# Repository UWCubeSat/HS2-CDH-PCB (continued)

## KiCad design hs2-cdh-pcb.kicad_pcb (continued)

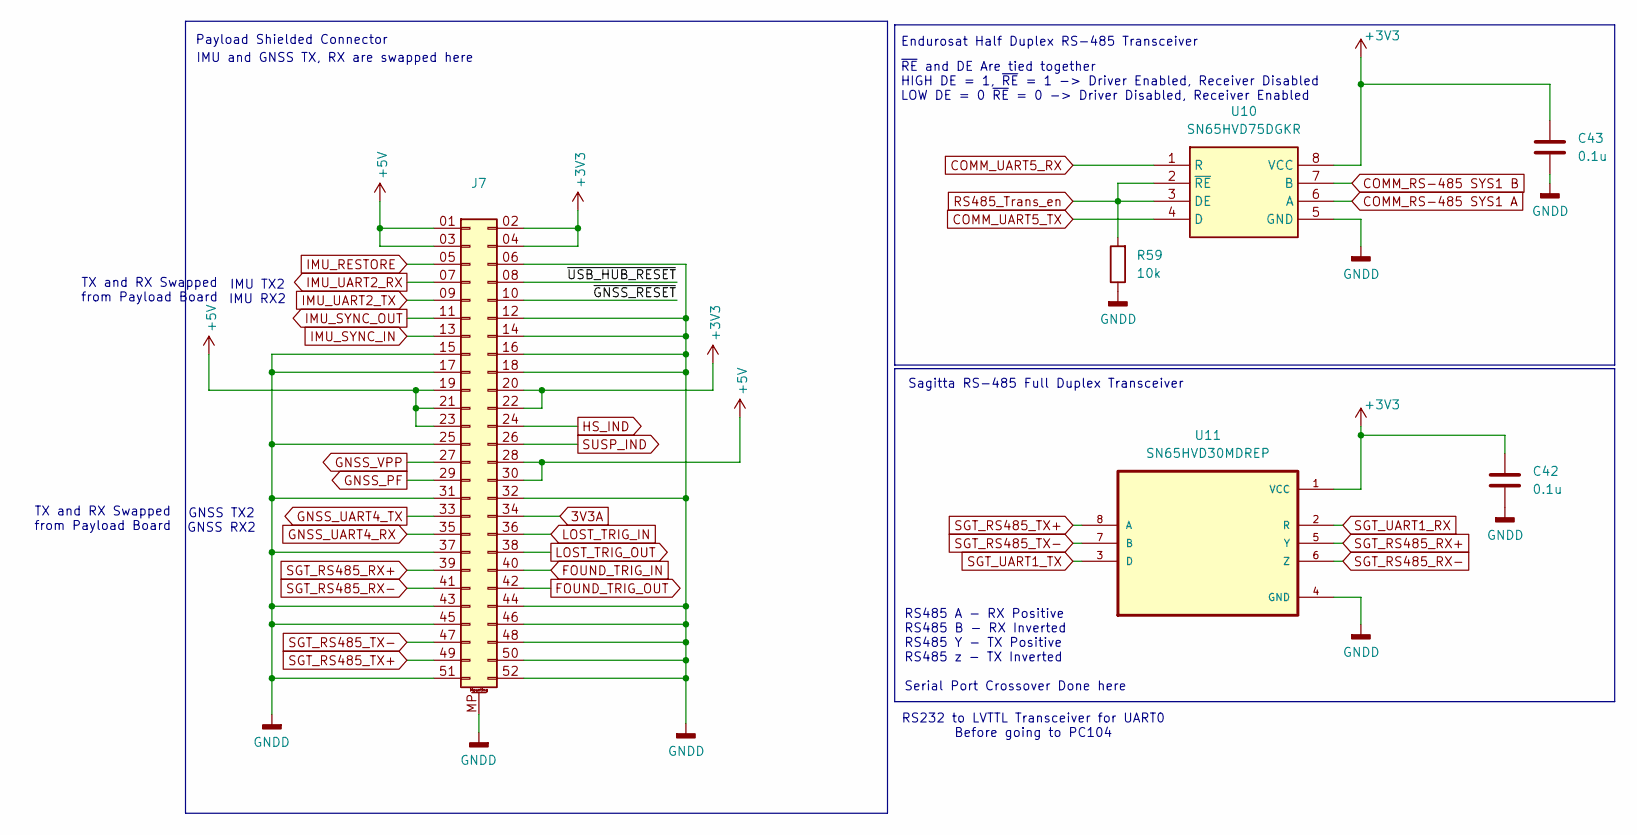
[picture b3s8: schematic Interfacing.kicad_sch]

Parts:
C42, C43: 0.1u; C_0603_1608Metric
J7: Conn_02x26_Odd_Even_MountingPin; SAMTEC_ASP-129637
R59: 10k; R_0603_1608Metric
U10: SN65HVD75DGKR; VSSOP-8_3x3mm_P0.65mm; Mouser Part Number 595-SN65HVD75DGKR
U11: SN65HVD30MDREP; SOIC-8_3.9x4.9mm_P1.27mm

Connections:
3V3A: J7.34; also elsewhere on the board
+3V3: C42.1, C43.1, J7.02 (Pin_2), J7.04 (Pin_4), J7.20, J7.22, U10.8 (VCC), U11.1 (VCC); also elsewhere on the board
+5V: J7.01 (Pin_1), J7.03 (Pin_3), J7.19, J7.21, J7.23, J7.28, J7.30; also elsewhere on the board
/Interfacing/~GNSS_RESET: J7.10
/Interfacing/~USB_HUB_RESET: J7.08 (Pin_8)
COMM_RS-485 SYS1 A: U10.6 (A); also elsewhere on the board
COMM_RS-485 SYS1 B: U10.7 (B); also elsewhere on the board
COMM_UART5_RX: U10.1 (R); also elsewhere on the board
COMM_UART5_TX: U10.4 (D); also elsewhere on the board
FOUND_TRIG_IN: J7.40; also elsewhere on the board
FOUND_TRIG_OUT: J7.42; also elsewhere on the board
GNDD: C42.2, C43.2, J7.06 (Pin_6), J7.12, J7.14, J7.15, J7.16, J7.17, J7.18, J7.25, J7.31, J7.32, J7.37, J7.43, J7.44, J7.45, J7.46, J7.48, J7.50, J7.51, J7.52, J7.MP (MountPin), R59.1, U10.5 (GND), U11.4 (GND); also elsewhere on the board
GNSS_PF: J7.29; also elsewhere on the board
GNSS_UART4_RX: J7.35; also elsewhere on the board
GNSS_UART4_TX: J7.33; also elsewhere on the board
GNSS_VPP: J7.27; also elsewhere on the board
HS_IND: J7.24; also elsewhere on the board
IMU_RESTORE: J7.05 (Pin_5)
IMU_SYNC_IN: J7.13; also elsewhere on the board
IMU_SYNC_OUT: J7.11; also elsewhere on the board
IMU_UART2_RX: J7.07 (Pin_7); also elsewhere on the board
IMU_UART2_TX: J7.09 (Pin_9); also elsewhere on the board
LOST_TRIG_IN: J7.36; also elsewhere on the board
LOST_TRIG_OUT: J7.38; also elsewhere on the board
RS485_Trans_en: R59.2, U10.2 (~RE), U10.3 (DE); also elsewhere on the board
SGT_RS485_RX+: J7.39, U11.5 (Y)
SGT_RS485_RX-: J7.41, U11.6 (Z)
SGT_RS485_TX+: J7.49, U11.8 (A)
SGT_RS485_TX-: J7.47, U11.7 (B)
SGT_UART1_RX: U11.2 (R); also elsewhere on the board
SGT_UART1_TX: U11.3 (D); also elsewhere on the board
SUSP_IND: J7.26; also elsewhere on the board

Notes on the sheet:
Sagitta RS-485 Full Duplex Transceiver
Payload Shielded Connector
IMU TX2 IMU RX2
GNSS TX2 GNSS RX2
TX and RX Swapped from Payload Board
~{RE} and DE Are tied together HIGH DE = 1, ~{RE} = 1 -> Driver Enabled, Receiver Disabled LOW DE = 0 ~{RE} = 0 -> Driver Disabled, Receiver Enabled
Endurosat Half Duplex RS-485 Transceiver
RS232 to LVTTL Transceiver for UART0 Before going to PC104
RS485 A - RX Positive RS485 B - RX Inverted RS485 Y - TX Positive RS485 z - TX Inverted Serial Port Crossover Done here
IMU and GNSS TX, RX are swapped here

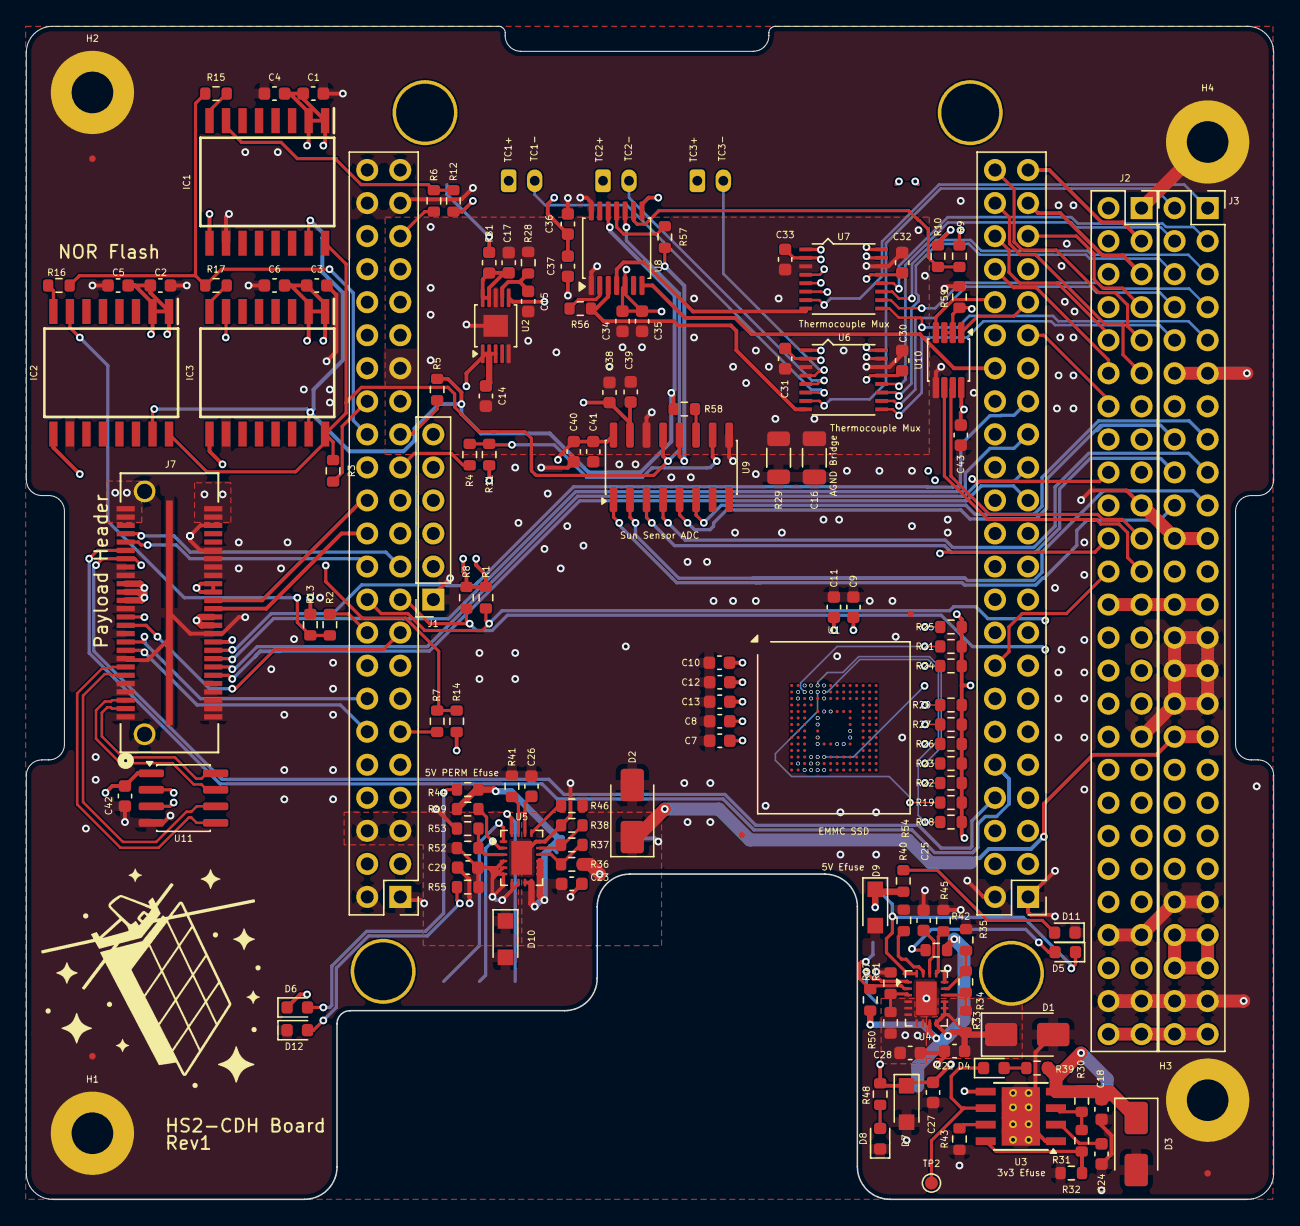
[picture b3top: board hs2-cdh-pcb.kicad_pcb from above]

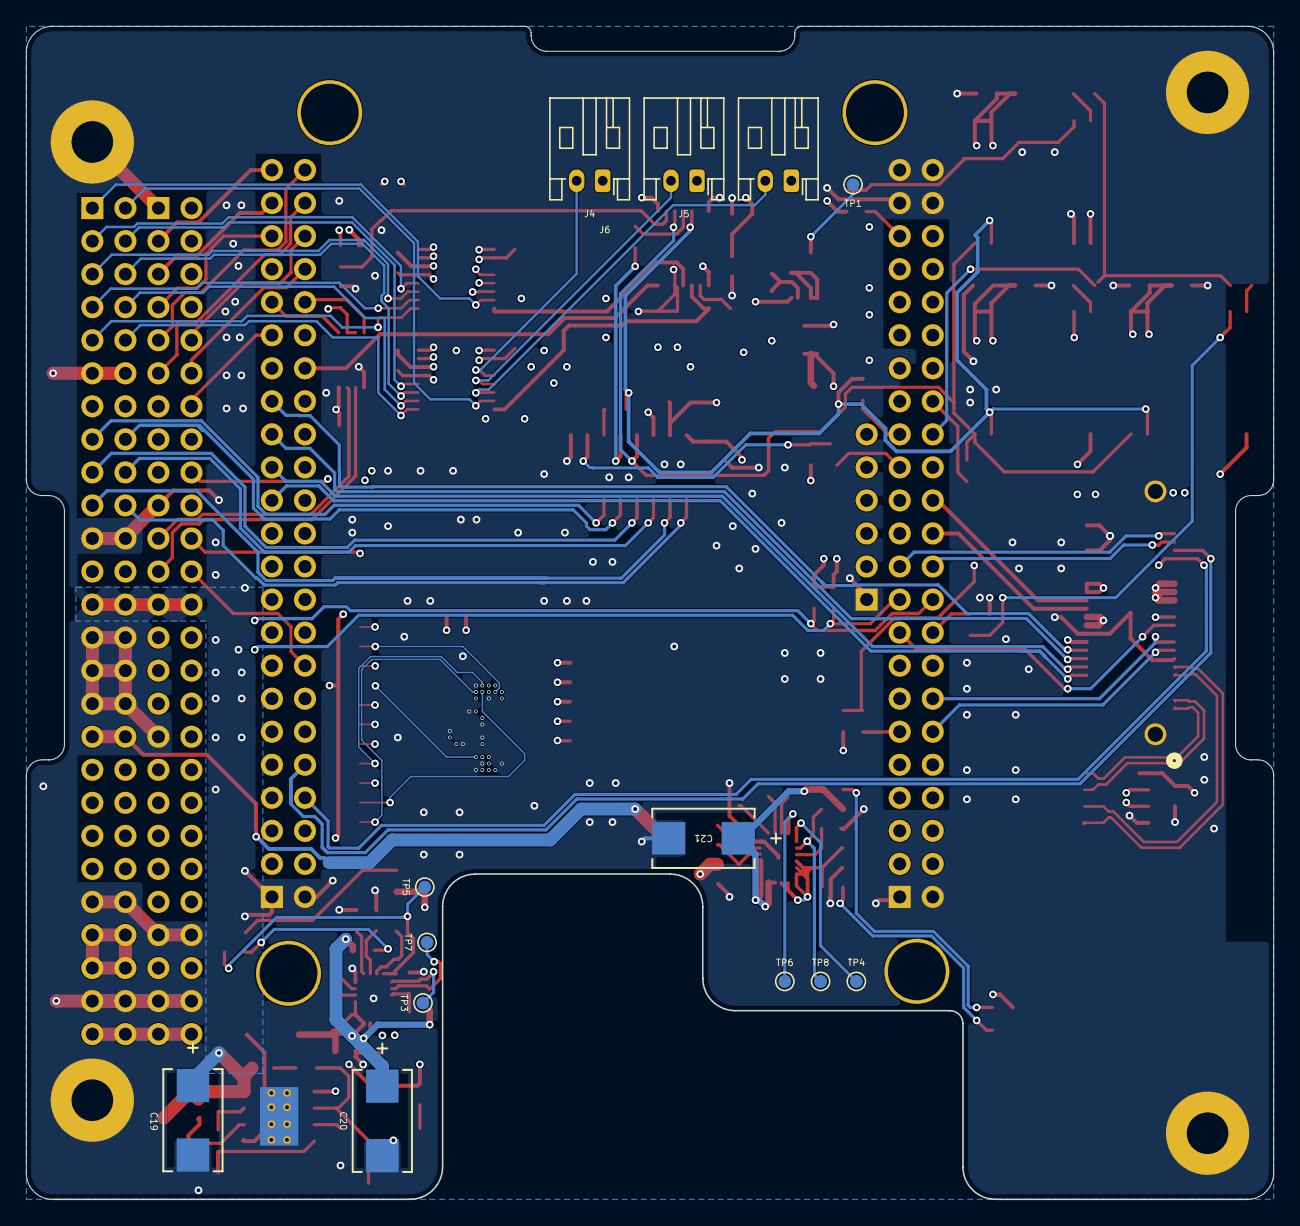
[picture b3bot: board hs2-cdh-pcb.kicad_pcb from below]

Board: 6 copper layers, 95.9 x 90.2 mm, 149 parts (13 on the bottom side), 148 nets.

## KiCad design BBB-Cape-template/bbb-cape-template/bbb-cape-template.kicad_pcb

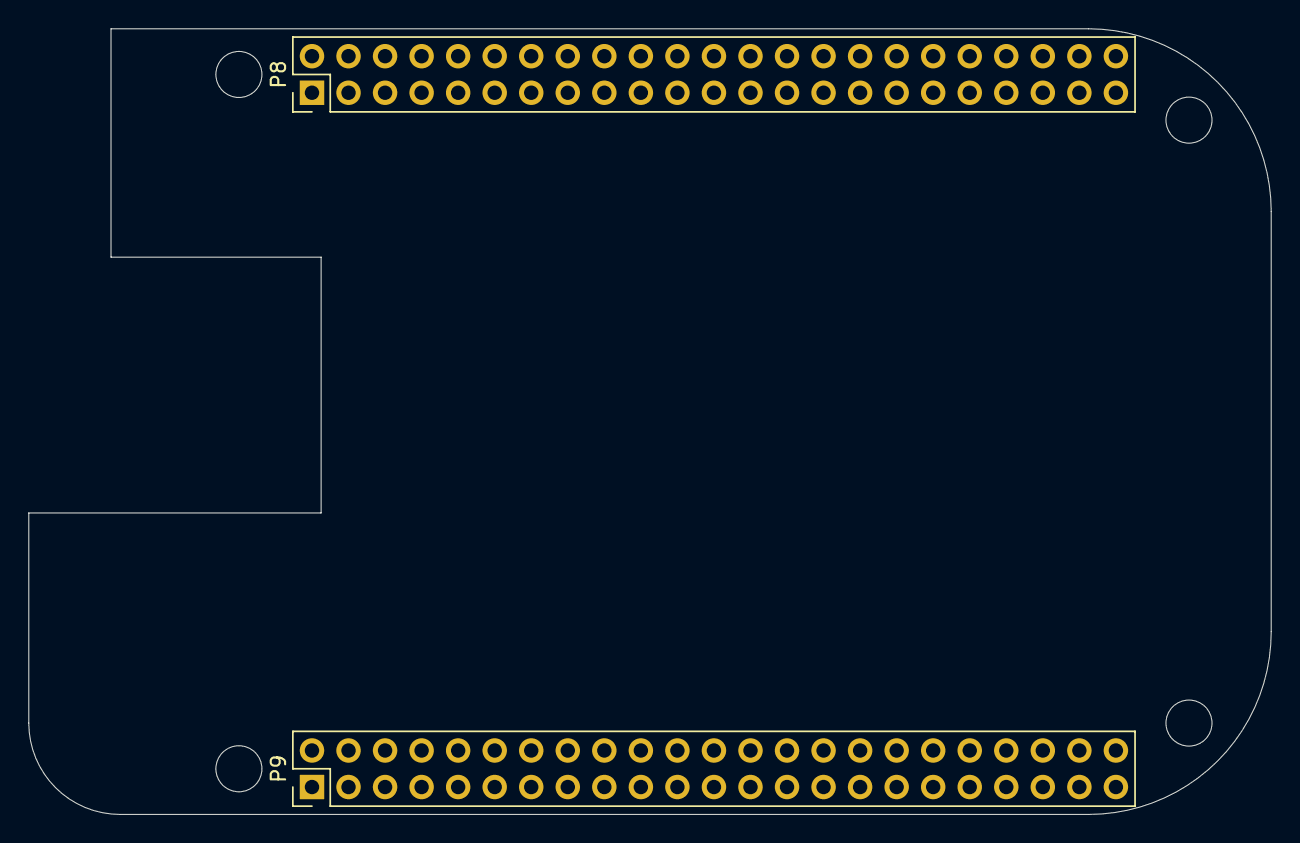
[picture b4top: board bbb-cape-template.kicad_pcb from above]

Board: 2 copper layers, 86.4 x 54.6 mm, 6 parts (0 on the bottom side), 4 nets, no tracks yet.

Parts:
MH1, MH2, MH3, MH4: MountingHole_3.2mm_M3_DIN965
P8, P9: BeagleBone_Black_Header; PinHeader_2x23_P2.54mm_Vertical

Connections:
+3V3: P9.3, P9.4
+5V: P9.5, P9.6
GNDD: P8.1, P8.2, P9.1, P9.2, P9.43, P9.44, P9.45, P9.46
VBUS: P9.7, P9.8

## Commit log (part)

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2026-05-20 initial commit with bbb template kicad project
2026-05-20 updated to kicad 10
2026-05-20 added memory chips schematic into library
2026-05-20 found graphs for memory chips
2026-05-20 added nor memory symbols
2026-05-25 Initial KiCad project structure and gitignore configuration
2026-05-26 Adding BBB cape and NOR flash ICs
2026-05-26 Pushing changes to top level after removing bbb cape and nor flash ics
2026-05-26 pulled PC104 from EPS board
2026-05-26 Adding power distribution schematic
2026-05-29 power distrubtion schematic, exact components tbd
2026-05-29 add thermal sheet
2026-05-30 oops forgot to add all changes from prev commits
